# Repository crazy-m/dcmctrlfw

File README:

DC Motor Control Firmware

Board based on AT90CAN128 and ATA6824 Brushed DC Motor MOSFET Driver.

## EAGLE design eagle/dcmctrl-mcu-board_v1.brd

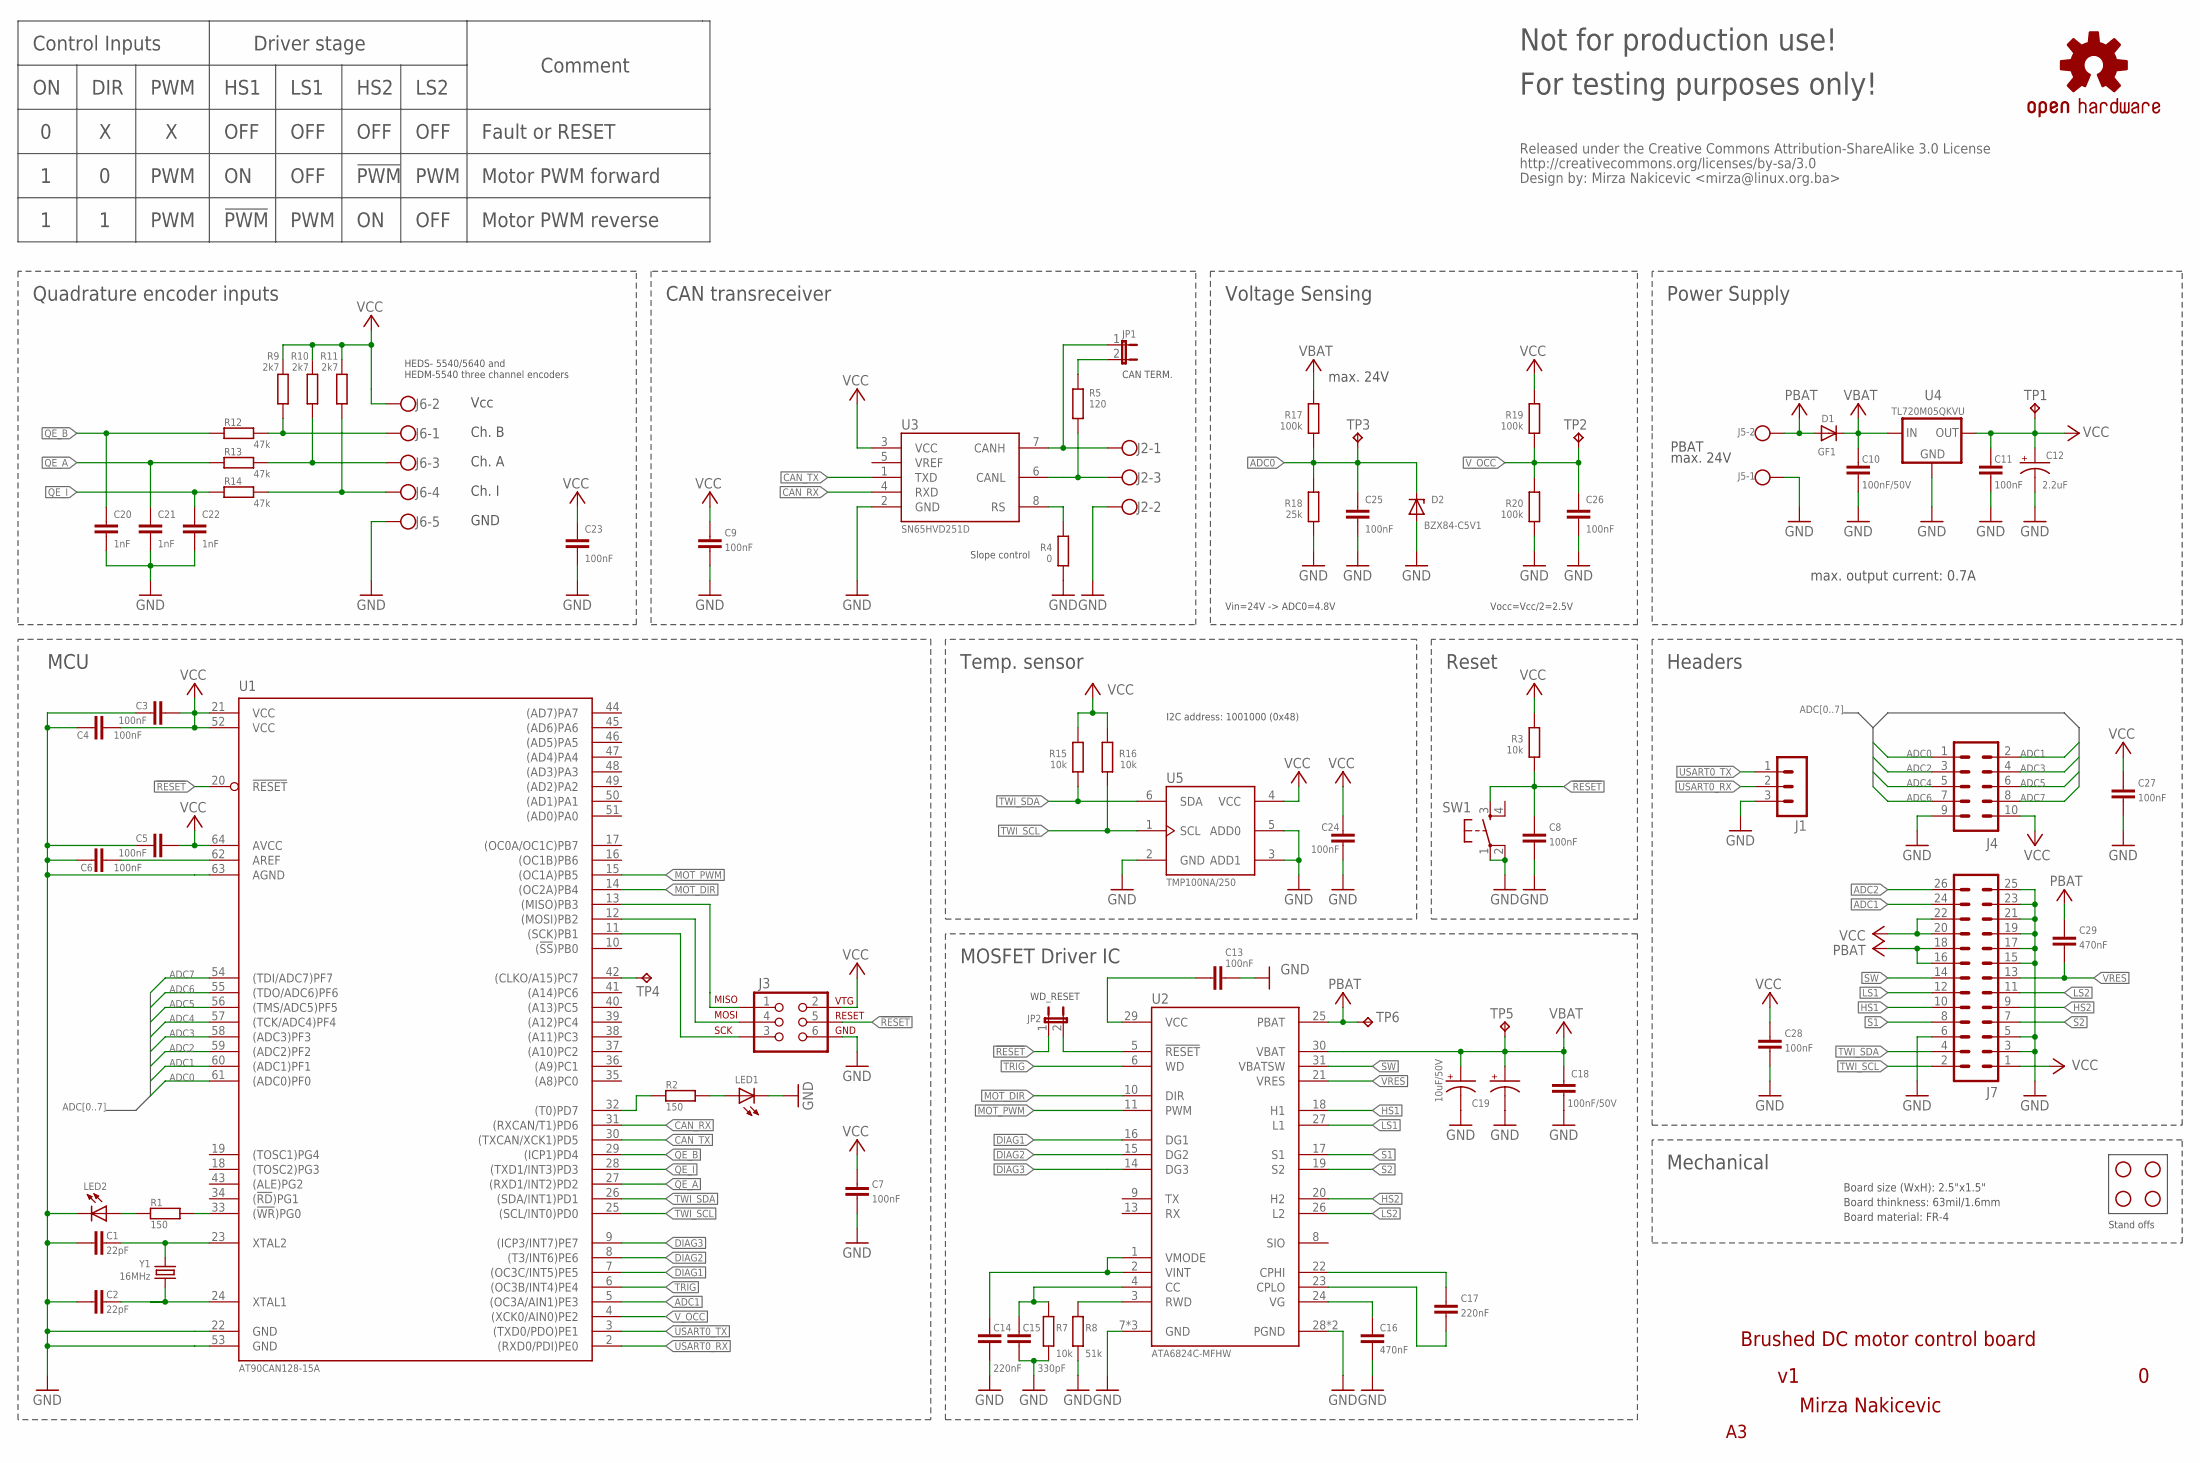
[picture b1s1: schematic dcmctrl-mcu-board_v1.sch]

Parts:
C1, C2: 22pF; C0603
C3, C4, C5, C6, C7, C8, C9, C11, C13, C23, C24, C25, C26, C27, C28: 100nF; C0603
C10, C18: 100nF/50V; C0603
C12: 2.2uF; EIA3216
C14, C17: 220nF; C0603
C15: 330pF; C0603
C16, C29: 470nF; C0603
C19: 10uF/50V; EIA3528
C20, C21, C22: 1nF; C0603
C999: 10uF/50V; RADIAL-1
D1: GF1; SMA-DO214AC
D2: BZX84-C5V1; TO236
J1: MA03-1
J2: BLOCK3-3.5-4UCON; 4UCON-20193
J3: AVR-ISP-6-100; 2X3-100
J4: MA05-2
J5: BLOCK2-3.5-4UCON; 4UCON-19963
J6: BLOCK5-3.5-4UCON; 4UCON-20223
J7: MA13-2
JP1: JUMPER-2PTH; 1X02
JP2: JUMPER-2SMD-NC; SJ_2S
LED1, LED2: LEDCHIPLED_0603; CHIPLED_0603
R1, R2: 150; R0603
R3, R7, R15, R16: 10k; R0603
R4: 0; R0603
R5: 120; R0805
R8: 51k; R0603
R9, R10, R11: 2k7; R0603
R12, R13, R14: 47k; R0603
R17, R19, R20: 100k; R0603
R18: 25k; R0603
SW1: TAC_SWITCHPTH; TACTILE-PTH
TP1, TP2, TP3, TP4, TP5, TP6: TPB1,27; B1,27
U1: AT90CAN128-15A; TQFP64
U2: ATA6824C-MFHW; TPQFP32
U3: SN65HVD251D; SO-08
U4: TL720M05QKVU; D-PAK_TO252AA
U5: TMP100NA/250; SOT23-6L
U$1, U$2, U$3, U$4: STAND-OFF
U$24: OSHW-LOGOM; OSHW-LOGO-M
U$29: CC-SA
Y1: 16MHz; HC49U-V

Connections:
!RESET: C8.1, J3.5, JP2.1, R3.1, SW1.3, U1.20 (!RESET)
ADC0: C25.1, D2.C, J4.1, R17.1, R18.2, TP3.TP, U1.61 ((ADC0)PF0)
ADC1: J4.2, J7.24, U1.5 ((OC3A/AIN1)PE3), U1.60 ((ADC1)PF1)
ADC2: J4.3, J7.26, U1.59 ((ADC2)PF2)
ADC3: J4.4, U1.58 ((ADC3)PF3)
ADC4: J4.5, U1.57 ((TCK/ADC4)PF4)
ADC5: J4.6, U1.56 ((TMS/ADC5)PF5)
ADC6: J4.7, U1.55 ((TDO/ADC6)PF6)
ADC7: J4.8, U1.54 ((TDI/ADC7)PF7)
CAN_H: J2.1, JP1.1, U3.7 (CANH)
CAN_L: J2.3, R5.2, U3.6 (CANL)
CAN_RX: U1.31 ((RXCAN/T1)PD6), U3.4 (RXD)
CAN_TX: U1.30 ((TXCAN/XCK1)PD5), U3.1 (TXD)
DIAG1: U1.7 ((OC3C/INT5)PE5), U2.16 (DG1)
DIAG2: U1.8 ((T3/INT6)PE6), U2.15 (DG2)
DIAG3: U1.9 ((ICP3/INT7)PE7), U2.14 (DG3)
GND: C1.2, C2.2, C3.2, C4.2, C5.2, C6.2, C7.2, C8.2, C9.2, C10.2, C11.2, C12.C (-), C13.2, C14.2, C15.2, C16.2, C18.2, C19.C (-), C20.2, C21.2, C22.2, C23.2, C24.2, C25.2, C26.2, C27.2, C28.2, C999.2 (-), D2.A, J1.3, J2.2, J3.6, J4.9, J5.1, J6.5, J7.3, J7.5, J7.6, J7.15, J7.17, J7.19, J7.21, J7.23, J7.25, LED1.C, LED2.C, R4.1, R7.1, R8.1, R18.1, R20.1, SW1.1, SW1.2, U1.22 (GND), U1.53 (GND), U1.63 (AGND), U2.7 (GND), U2.12 (GND), U2.28 (PGND), U2.32 (GND), U2.33 (PGND), U3.2 (GND), U4.4 (GND), U5.2 (GND), U5.3 (ADD1), U5.5 (ADD0)
HS1: J7.10, U2.18 (H1)
HS2: J7.9, U2.20 (H2)
LS1: J7.12, U2.27 (L1)
LS2: J7.11, U2.26 (L2)
MOT_DIR: U1.14 ((OC2A)PB4), U2.10 (DIR)
MOT_PWM: U1.15 ((OC1A)PB5), U2.11 (PWM)
unnamed: C1.1, U1.23 (XTAL2), Y1.1
unnamed: C2.1, U1.24 (XTAL1), Y1.2
unnamed: R4.2, U3.8 (RS)
unnamed: JP1.2, R5.1
unnamed: R1.2, U1.33 ((!WR!)PG0)
unnamed: C15.1, R7.2, U2.4 (CC)
unnamed: J3.1, U1.13 ((MISO)PB3)
unnamed: R8.2, U2.3 (RWD)
unnamed: C14.1, U2.1 (VMODE), U2.2 (VINT)
unnamed: C16.1, U2.24 (VG)
unnamed: C17.2, U2.23 (CPLO)
unnamed: C17.1, U2.22 (CPHI)
unnamed: C6.1, U1.62 (AREF)
unnamed: J3.4, U1.12 ((MOSI)PB2)
unnamed: J3.3, U1.11 ((SCK)PB1)
unnamed: TP4.TP, U1.42 ((CLKO/A15)PC7)
unnamed: C13.1, U2.29 (VCC)
unnamed: LED2.A, R1.1
unnamed: R2.2, U1.32 ((T0)PD7)
unnamed: LED1.A, R2.1
PBAT: C29.1, D1.A, J5.2, J7.16, J7.18, TP6.TP, U2.25 (PBAT)
QE_A: C21.1, R13.1, U1.27 ((RXD1/INT2)PD2)
QE_A_IN: J6.3, R10.1, R13.2
QE_B: C20.1, R12.1, U1.29 ((ICP1)PD4)
QE_B_IN: J6.1, R9.1, R12.2
QE_I: C22.1, R14.1, U1.28 ((TXD1/INT3)PD3)
QE_I_IN: J6.4, R11.1, R14.2
S1: J7.8, U2.17 (S1)
S2: J7.7, U2.19 (S2)
SW: J7.14, U2.31 (VBATSW)
TRIG: U1.6 ((OC3B/INT4)PE4), U2.6 (WD)
TWI_SCL: J7.2, R16.1, U1.25 ((SCL/INT0)PD0), U5.1 (SCL)
TWI_SDA: J7.4, R15.1, U1.26 ((SDA/INT1)PD1), U5.6 (SDA)
USART0_RX: J1.2, U1.2 ((RXD0/PDI)PE0)
USART0_TX: J1.1, U1.3 ((TXD0/PDO)PE1)
VBAT: C10.1, C18.1, C19.A (+), C999.1 (+), D1.K (C), R17.2, TP5.TP, U2.30 (VBAT), U4.1 (IN)
VCC: C3.1, C4.1, C5.1, C7.1, C9.1, C11.1, C12.A (+), C23.1, C24.1, C27.1, C28.1, J3.2, J4.10, J6.2, J7.1, J7.20, J7.22, R3.2, R9.2, R10.2, R11.2, R15.2, R16.2, R19.2, TP1.TP, U1.21 (VCC), U1.52 (VCC), U1.64 (AVCC), U3.3 (VCC), U4.3 (OUT), U5.4 (VCC)
VRES: C29.2, J7.13, U2.21 (VRES)
V_OCC: C26.1, R19.1, R20.2, TP2.TP, U1.4 ((XCK0/AIN0)PE2)
WD_RESET: JP2.2, U2.5 (!RESET)

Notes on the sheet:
MCU
Reset
Power Supply
Voltage Sensing
Quadrature encoder inputs
Headers
MOSFET Driver IC
CAN transreceiver
Temp. sensor
Brushed DC motor control board
Mirza Nakicevic
WD_RESET
CAN TERM.
Control Inputs
DIR
PWM
Driver stage
HS1
LS1
HS2
LS2
OFF
!PWM
Comment
Fault or RESET
Motor PWM forward
Motor PWM reverse
Slope control
Mechanical
Board size (WxH): 2.5"x1.5"
Board material: FR-4
Board thinkness: 63mil/1.6mm
Not for production use!
For testing purposes only!
max. 24V
Vin=24V -> ADC0=4.8V
Vocc=Vcc/2=2.5V
Vcc
Ch. B
Ch. A

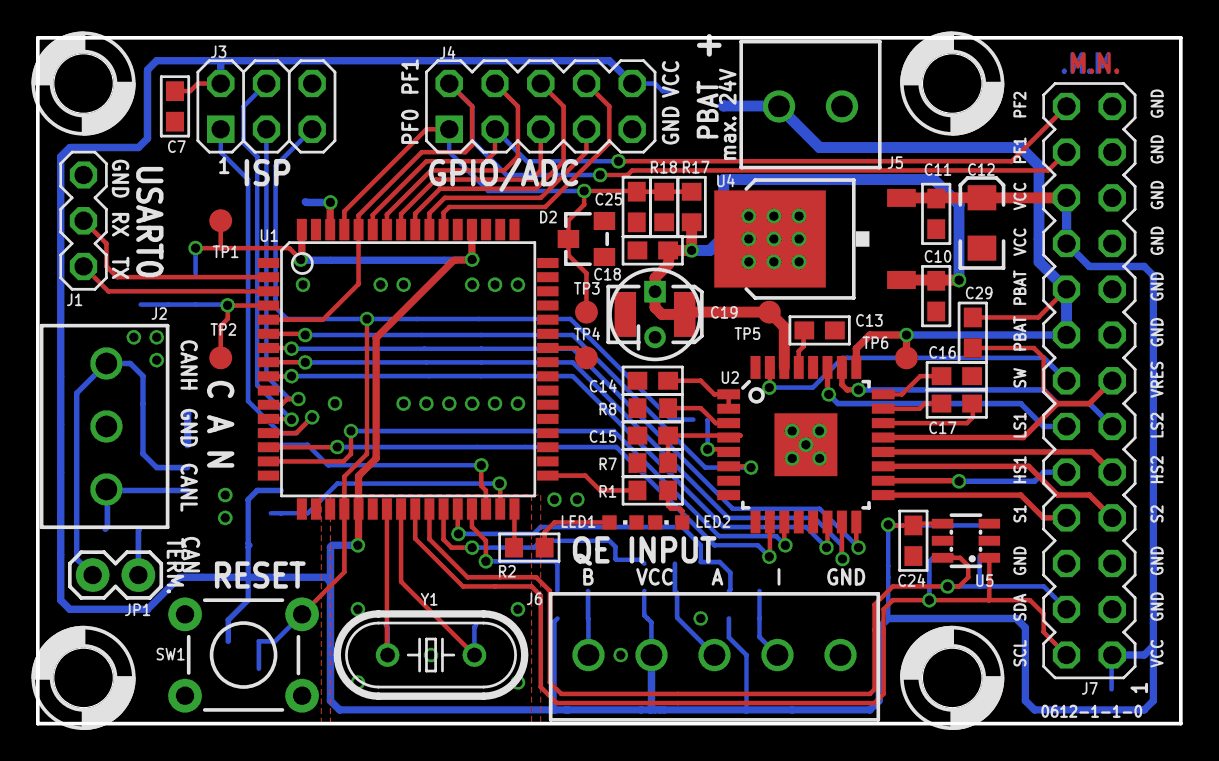
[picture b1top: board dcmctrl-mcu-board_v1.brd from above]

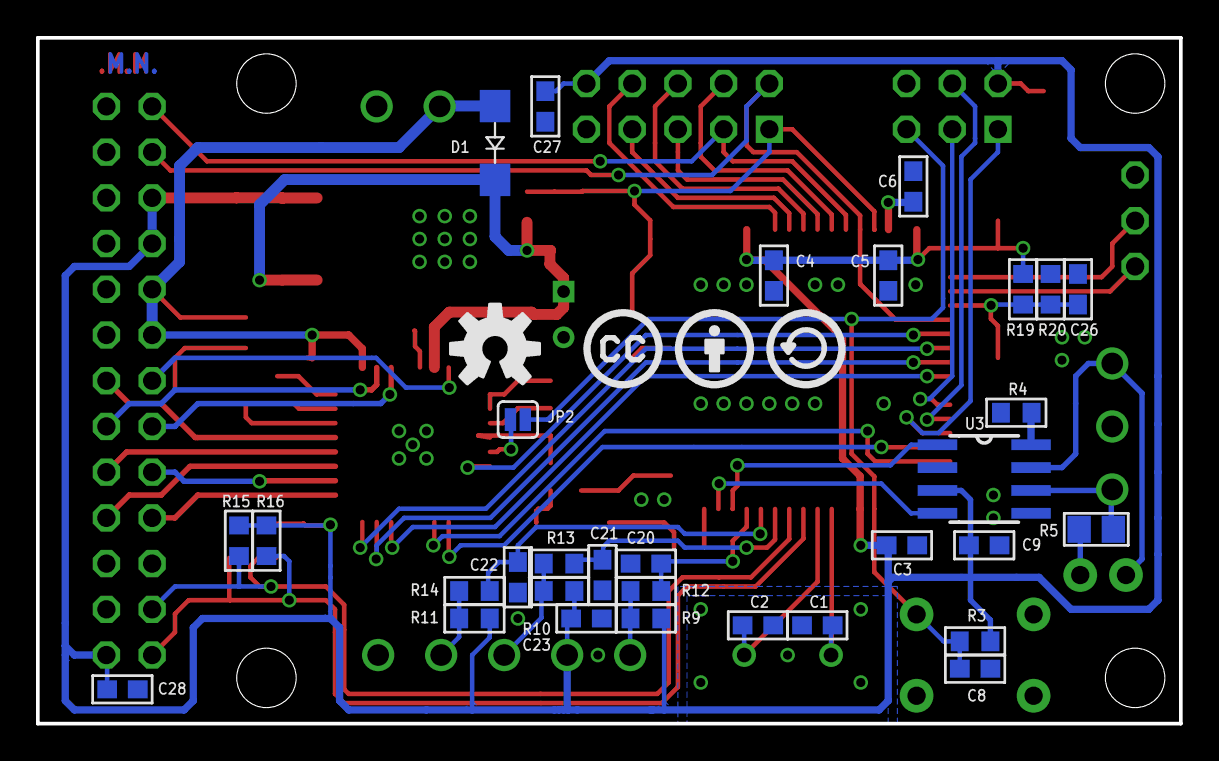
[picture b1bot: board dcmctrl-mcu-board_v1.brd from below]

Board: 2 copper layers, 63.5 x 38.1 mm, 81 parts (33 on the bottom side), 63 nets.

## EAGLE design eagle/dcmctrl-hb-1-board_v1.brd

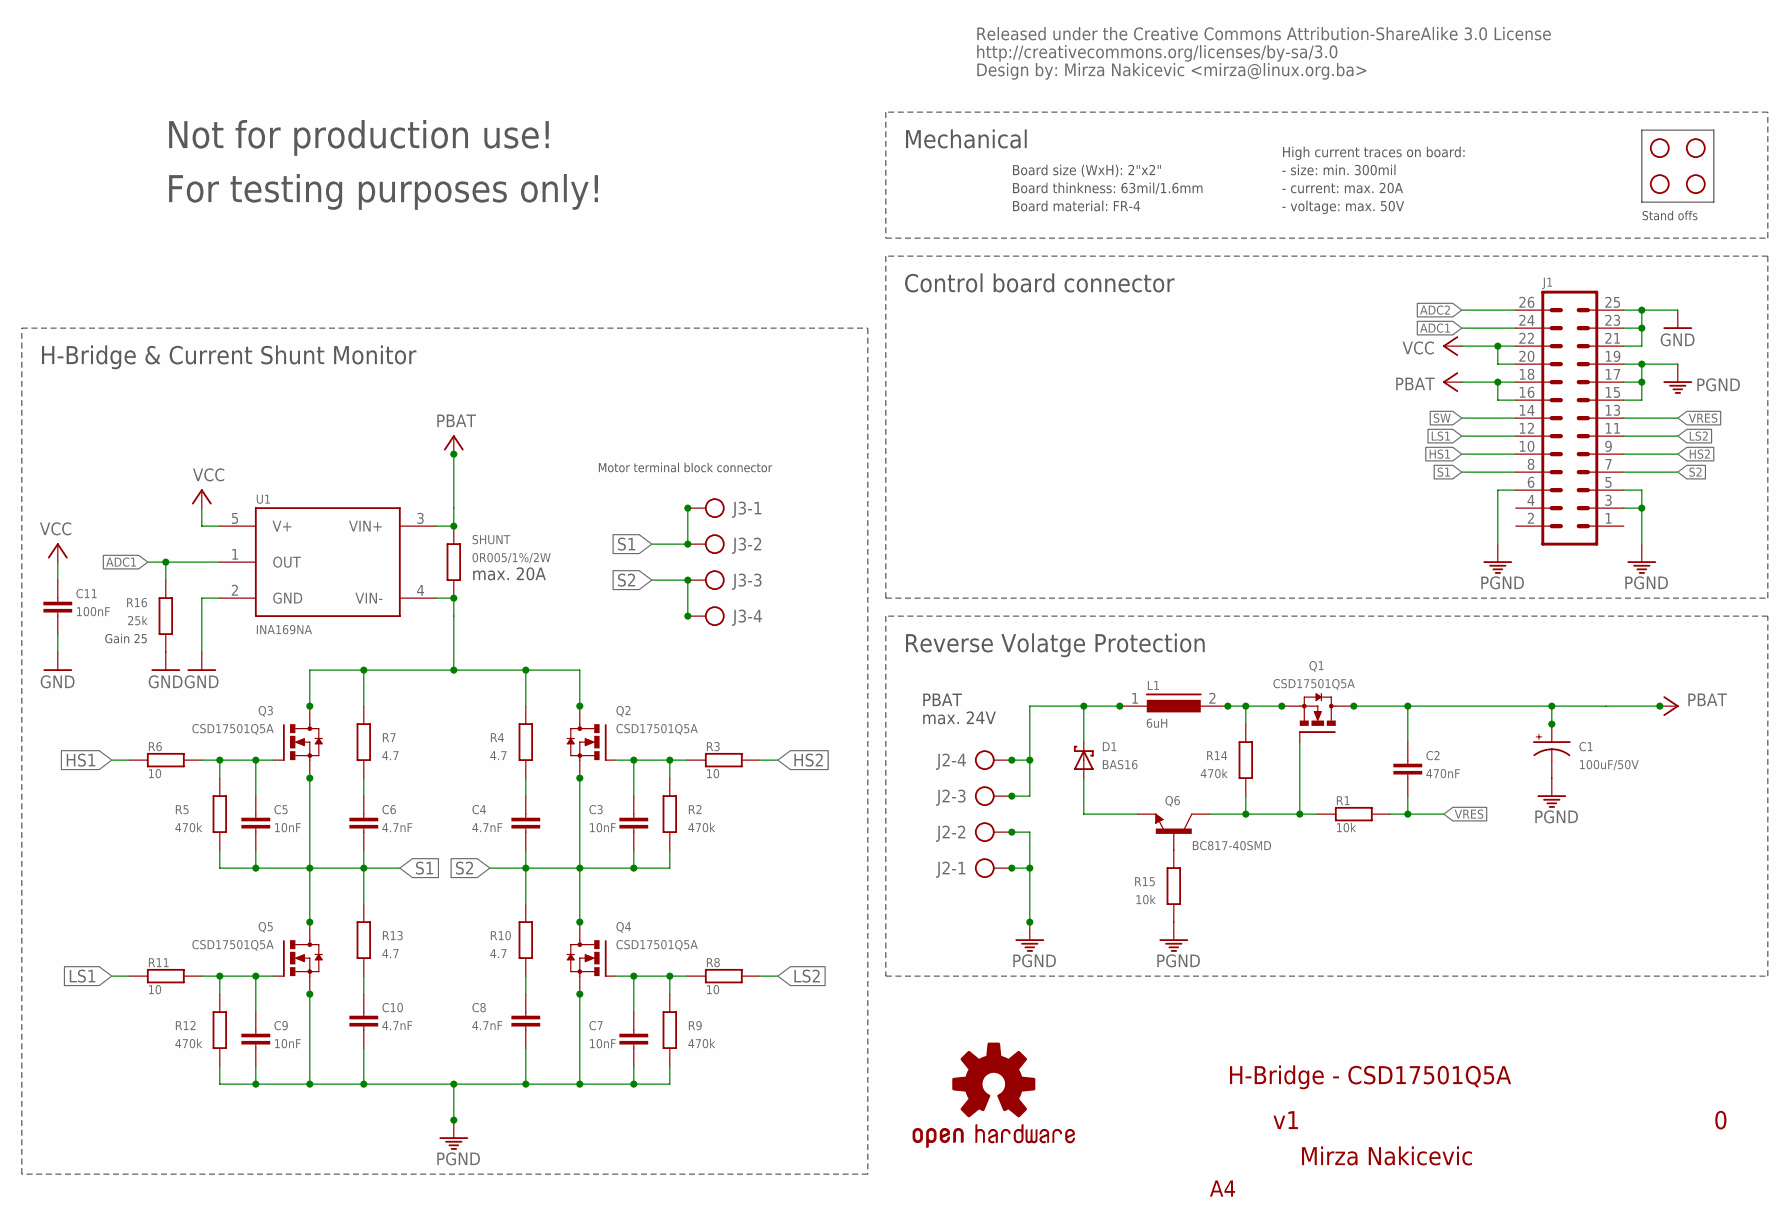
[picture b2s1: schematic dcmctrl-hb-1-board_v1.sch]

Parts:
C1: 100uF/50V; E5-13
C2: 470nF; C0603
C3, C5, C7, C9: 10nF; C0603
C4, C6, C8, C10: 4.7nF; C0603
C11: 100nF; C0603
D1: BAS16; SOT23
J1: MA13-2
J2, J3: W237-4
L1: 6uH; DR127
Q1, Q2, Q3, Q4, Q5: CSD17501Q5A; Q5A
Q6: BC817-40SMD; SOT23-BEC
R1, R15: 10k; R0603
R2, R5, R9, R12, R14: 470k; R0603
R3, R6, R8, R11: 10; R0603
R4, R7, R10, R13: 4.7; R0603
R16: 25k; R0603
SHUNT: 0R005/1%/2W; R2512
U1: INA169NA; SOT23-5
U$2, U$3, U$4, U$6: STAND-OFF
U$9: CC-SA
U$10: OSHW-LOGOM; OSHW-LOGO-M

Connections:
ADC1: J1.24, R16.2, U1.1 (OUT)
ADC2: J1.26
GND: C11.2, J1.21, J1.23, J1.25, R16.1, U1.2 (GND)
HS1: J1.10, R6.1
HS2: J1.9, R3.2
LS1: J1.12, R11.1
LS2: J1.11, R8.2
unnamed: C5.1, Q3.4 (G), R5.2, R6.2
unnamed: Q6.B, R15.2
unnamed: C9.1, Q5.4 (G), R11.2, R12.2
unnamed: C7.1, Q4.4 (G), R8.1, R9.2
unnamed: C3.1, Q2.4 (G), R2.2, R3.1
unnamed: C6.1, R7.1
unnamed: D1.1 (A), Q6.E
unnamed: C10.1, R13.1
unnamed: Q1.4 (G), Q6.C, R1.1, R14.1
unnamed: C8.1, R10.1
unnamed: C4.1, R4.1
PBAT: C1.+, C2.1, J1.16, J1.18, Q1.5 (D), Q1.6 (D), Q1.7 (D), Q1.8 (D), Q1.TP (D), SHUNT.2, U1.3 (VIN+)
PBAT-: Q2.5 (D), Q2.6 (D), Q2.7 (D), Q2.8 (D), Q2.TP (D), Q3.5 (D), Q3.6 (D), Q3.7 (D), Q3.8 (D), Q3.TP (D), R4.2, R7.2, SHUNT.1, U1.4 (VIN-)
PGND: C1.-, C7.2, C8.2, C9.2, C10.2, J1.3, J1.5, J1.6, J1.15, J1.17, J1.19, J2.1, J2.2, Q4.1 (S), Q4.2 (S), Q4.3 (S), Q5.1 (S), Q5.2 (S), Q5.3 (S), R9.1, R12.1, R15.1
S1: C5.2, C6.2, J1.8, J3.1, J3.2, Q3.1 (S), Q3.2 (S), Q3.3 (S), Q5.5 (D), Q5.6 (D), Q5.7 (D), Q5.8 (D), Q5.TP (D), R5.1, R13.2
S2: C3.2, C4.2, J1.7, J3.3, J3.4, Q2.1 (S), Q2.2 (S), Q2.3 (S), Q4.5 (D), Q4.6 (D), Q4.7 (D), Q4.8 (D), Q4.TP (D), R2.1, R10.2
SW: J1.14
VCC: C11.1, J1.20, J1.22, U1.5 (V+)
VIN: D1.3 (C), J2.3, J2.4, L1.1
VIN2: L1.2, Q1.1 (S), Q1.2 (S), Q1.3 (S), R14.2
VRES: C2.2, J1.13, R1.2

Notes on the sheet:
H-Bridge & Current Shunt Monitor
Not for production use!
For testing purposes only!
Control board connector
Reverse Volatge Protection
max. 24V
PBAT
max. 20A
Gain 25
Mechanical
Board size (WxH): 2"x2"
Board material: FR-4
Board thinkness: 63mil/1.6mm
- size: min. 300mil
- current: max. 20A
- voltage: max. 50V
High current traces on board:
Motor terminal block connector
H-Bridge - CSD17501Q5A
Mirza Nakicevic
Stand offs

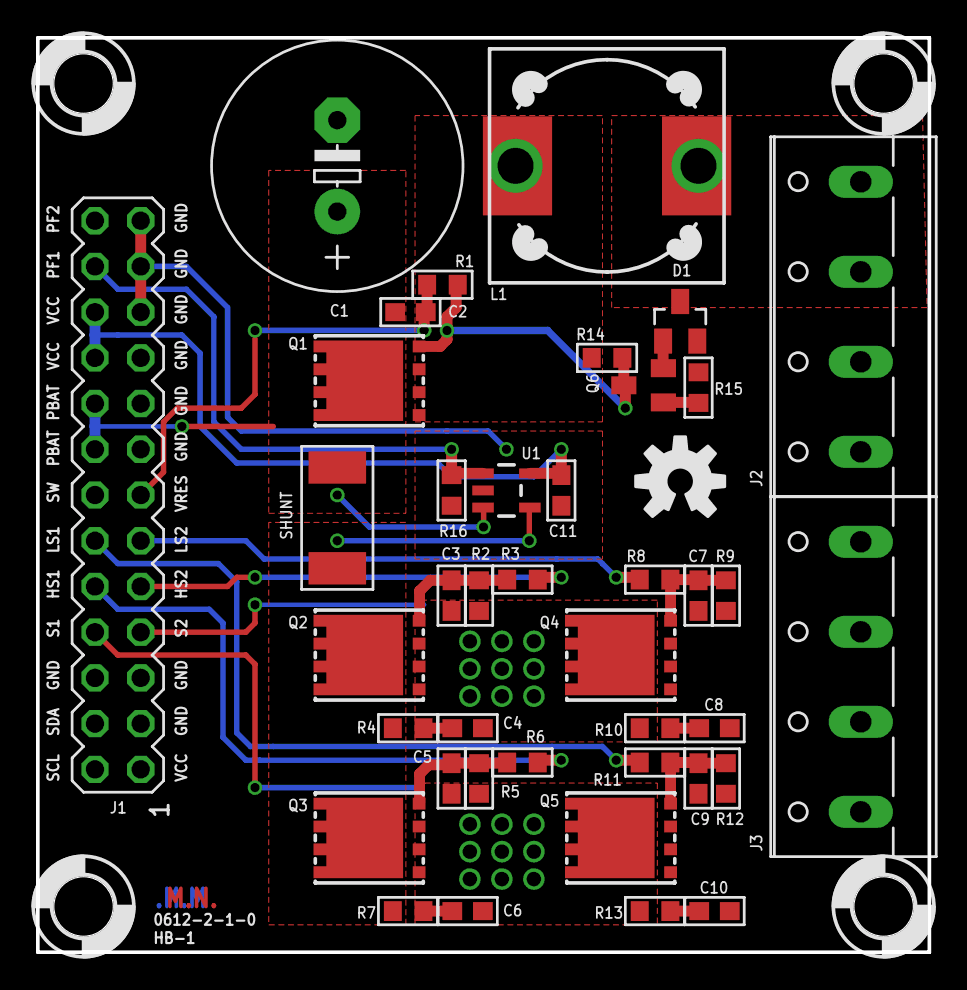
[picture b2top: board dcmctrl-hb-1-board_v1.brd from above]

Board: 2 copper layers, 49.5 x 50.8 mm, 46 parts (1 on the bottom side), 26 nets.

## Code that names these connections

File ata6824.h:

/*
 * dcmctrlfw - DC Motor Control firmware
 * Copyright (C) 2012 Mirza Nakicevic <mirza@linux.org.ba>
 *
 * This file is part of dcmctrlfw.
 *
 * dcmctrlfw is free software: you can redistribute it and/or modify
 * it under the terms of the GNU General Public License as published by
 * the Free Software Foundation, either version 3 of the License, or
 * (at your option) any later version.
 *
 * dcmctrlfw is distributed in the hope that it will be useful,
 * but WITHOUT ANY WARRANTY; without even the implied warranty of
 * MERCHANTABILITY or FITNESS FOR A PARTICULAR PURPOSE.  See the
 * GNU General Public License for more details.
 *
 * You should have received a copy of the GNU General Public License
 * along with dcmctrlfw. If not, see <http://www.gnu.org/licenses/>.
 */

#ifndef _ATA6824_H_
#define _ATA6824_H_

#define ATA6824_PWM_DDR  DDRB
#define ATA6824_PWM_PORT PORTB
#define ATA6824_PWM_PIN  PINB
#define ATA6824_PWM_PIO  PB5

#define ATA6824_DIR_DDR  DDRB
#define ATA6824_DIR_PORT PORTB
#define ATA6824_DIR_PIN  PINB
#define ATA6824_DIR_PIO  PB4

#define ATA6824_TRIG_DDR  DDRE
#define ATA6824_TRIG_PORT PORTE
#define ATA6824_TRIG_PIN  PINE
#define ATA6824_TRIG_PIO  PE4

#define ATA6824_DIAG1_DDR  DDRE
#define ATA6824_DIAG1_PORT PORTE
#define ATA6824_DIAG1_PIN  PINE
#define ATA6824_DIAG1_PIO  PE5

#define ATA6824_DIAG1_INT  INT5
#define ATA6824_DIAG1_ISC  ISC51
#define ATA6824_DIAG1_VECT INT5_vect

#define ATA6824_DIAG2_DDR  DDRE
#define ATA6824_DIAG2_PORT PORTE
#define ATA6824_DIAG2_PIN  PINE
#define ATA6824_DIAG2_PIO  PE6

#define ATA6824_DIAG2_INT  INT6
#define ATA6824_DIAG2_ISC  ISC61
#define ATA6824_DIAG2_VECT INT6_vect

#define ATA6824_DIAG3_DDR  DDRE
#define ATA6824_DIAG3_PORT PORTE
#define ATA6824_DIAG3_PIN  PINE
#define ATA6824_DIAG3_PIO  PE7

#define ATA6824_DIAG3_INT  INT7
#define ATA6824_DIAG3_ISC  ISC71
#define ATA6824_DIAG3_VECT INT7_vect

//#define ATA6824_PWM_FREQ 7820UL // TOP=1023
#define ATA6824_PWM_FREQ 20000UL
#define ATA6824_PWM_PRESCALE 1
#define ATA6824_PWM_TOP ( F_CPU/(2*ATA6824_PWM_PRESCALE*ATA6824_PWM_FREQ) )

#define FORWARD 0x00
#define REVERSE 0x01

/*
typedef enum
{
	FORWARD,
	REVERSE,
} ata6824_dir_t;
*/

typedef enum
{
	NO_FAILURE,
	WARNING,
	LATCHED_FAILURE
} ata6824_failure_t;

typedef struct
{
	ata6824_failure_t diag1;
	ata6824_failure_t diag2;
	ata6824_failure_t diag3;
} ata6824_diag_mgt_t;

void ata6824_init(void);
void ata6824_set_pwm(uint8_t pwm);
uint8_t ata6824_get_pwm(void);
void ata6824_set_dir(uint8_t dir);
uint8_t ata6824_get_dir(void);

#endif /* _ATA6824_H_ */

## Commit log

2012-07-29 some code cleanup...
2012-09-19 some changes to the code
2012-09-19 some more changes...

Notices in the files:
parts and their libraries:
other: Released under the Creative Commons Attribution-ShareAlike 3.0 License
other: http://creativecommons.org/licenses/by-sa/3.0
